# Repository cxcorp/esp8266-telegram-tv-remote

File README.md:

# esp8266-telegram-tv-remote

ESP8266 Telegram Bot which lets me control my TV with an IR LED.

## Assembly

PCB from JLCPCB.

### Schematic

### Breadboard

### Layout

### Renders

## License

The Arduino project under `esp8266-telegram-tv-remote/` is licensed under GPLv3. See COPYING under said directory.

The KiCAD project under `kicad/` is not licensed for now.

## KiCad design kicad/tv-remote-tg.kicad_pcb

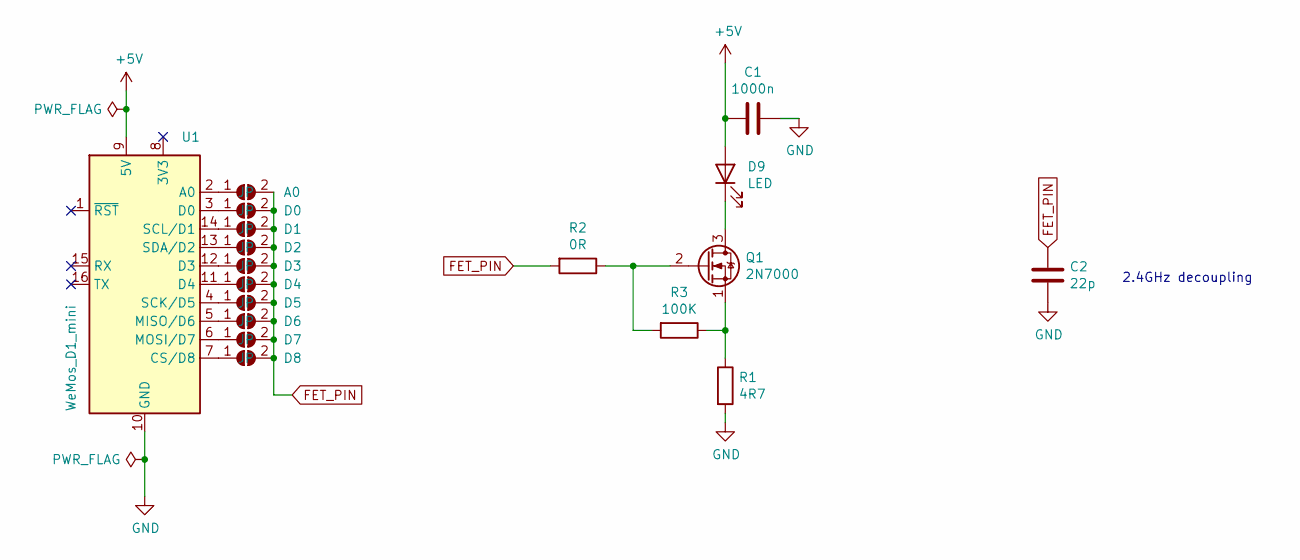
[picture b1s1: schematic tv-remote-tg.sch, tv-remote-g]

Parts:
A0: JP; SolderJumper-2_P1.3mm_Open_TrianglePad1.0x1.5mm
C1: 1000n; C_0603_1608Metric_Pad1.05x0.95mm_HandSolder
C2: 22p; C_0603_1608Metric_Pad1.05x0.95mm_HandSolder
D0, D1, D2, D3, D4, D5, D6, D7, D8: JP; SolderJumper-2_P1.3mm_Open_TrianglePad1.0x1.5mm
D9: LED; PinHeader_1x02_P2.54mm_Vertical
Q1: 2N7000; TO-92_Inline
R1: 4R7; R_0603_1608Metric_Pad1.05x0.95mm_HandSolder
R2: 0R; R_0603_1608Metric_Pad1.05x0.95mm_HandSolder
R3: 100K; R_0603_1608Metric_Pad1.05x0.95mm_HandSolder
U1: WeMos_D1_mini; WEMOS_D1_mini_light

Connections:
+5V: C1.1, D9.2 (A), U1.9 (5V)
FET_PIN: A0.2 (B), C2.1, D0.2 (B), D1.2 (B), D2.2 (B), D3.2 (B), D4.2 (B), D5.2 (B), D6.2 (B), D7.2 (B), D8.2 (B), R2.2
GND: C1.2, C2.2, R1.2, U1.10 (GND)
unnamed: A0.1 (A), U1.2 (A0)
unnamed: D0.1 (A), U1.3 (D0)
unnamed: D1.1 (A), U1.14 (SCL/D1)
unnamed: D2.1 (A), U1.13 (SDA/D2)
unnamed: D3.1 (A), U1.12 (D3)
unnamed: D4.1 (A), U1.11 (D4)
unnamed: D5.1 (A), U1.4 (SCK/D5)
unnamed: D6.1 (A), U1.5 (MISO/D6)
unnamed: D7.1 (A), U1.6 (MOSI/D7)
unnamed: D8.1 (A), U1.7 (CS/D8)
unnamed: D9.1 (K), Q1.3 (D)
unnamed: Q1.1 (S), R1.1, R3.1
unnamed: Q1.2 (G), R2.1, R3.2

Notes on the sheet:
2.4GHz decoupling

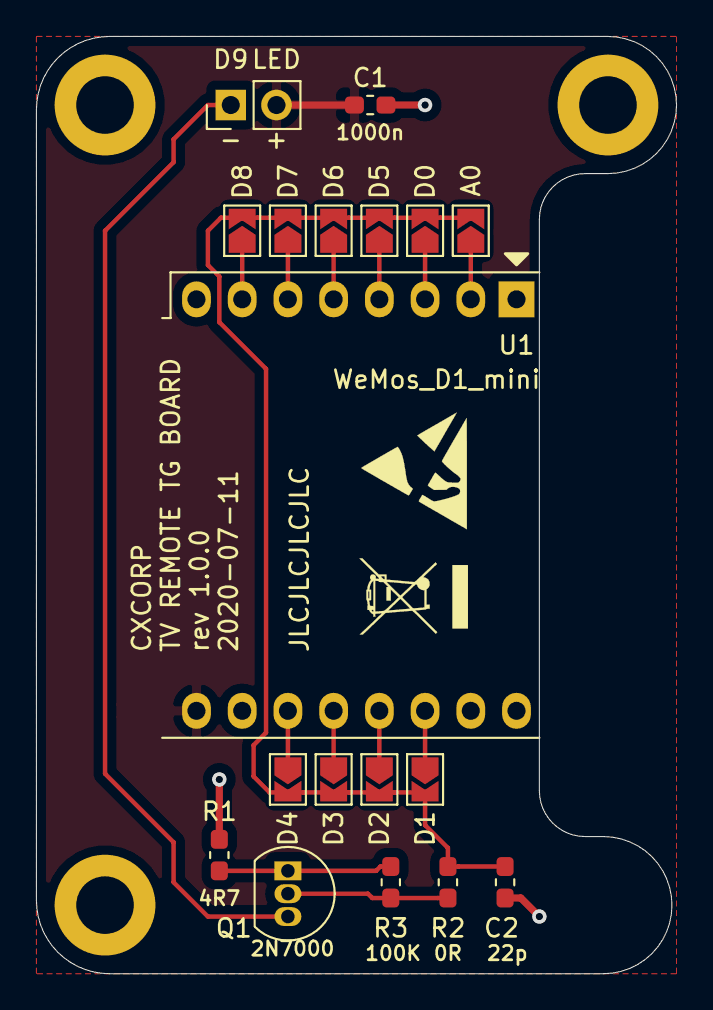
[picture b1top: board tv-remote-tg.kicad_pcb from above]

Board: 2 copper layers, 35.6 x 52.1 mm, 18 parts (0 on the bottom side), 16 nets.

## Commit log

2020-07-11 oops
2020-07-11 Add images
2020-07-11 Add images to README
2020-07-11 Move code under own dir
2020-07-11 Add kicad project
2020-07-11 Add breadboard image
2020-08-17 Add buttons to remote
    Add PWR, VOL_UP, VOL_DOWN and MUTE
